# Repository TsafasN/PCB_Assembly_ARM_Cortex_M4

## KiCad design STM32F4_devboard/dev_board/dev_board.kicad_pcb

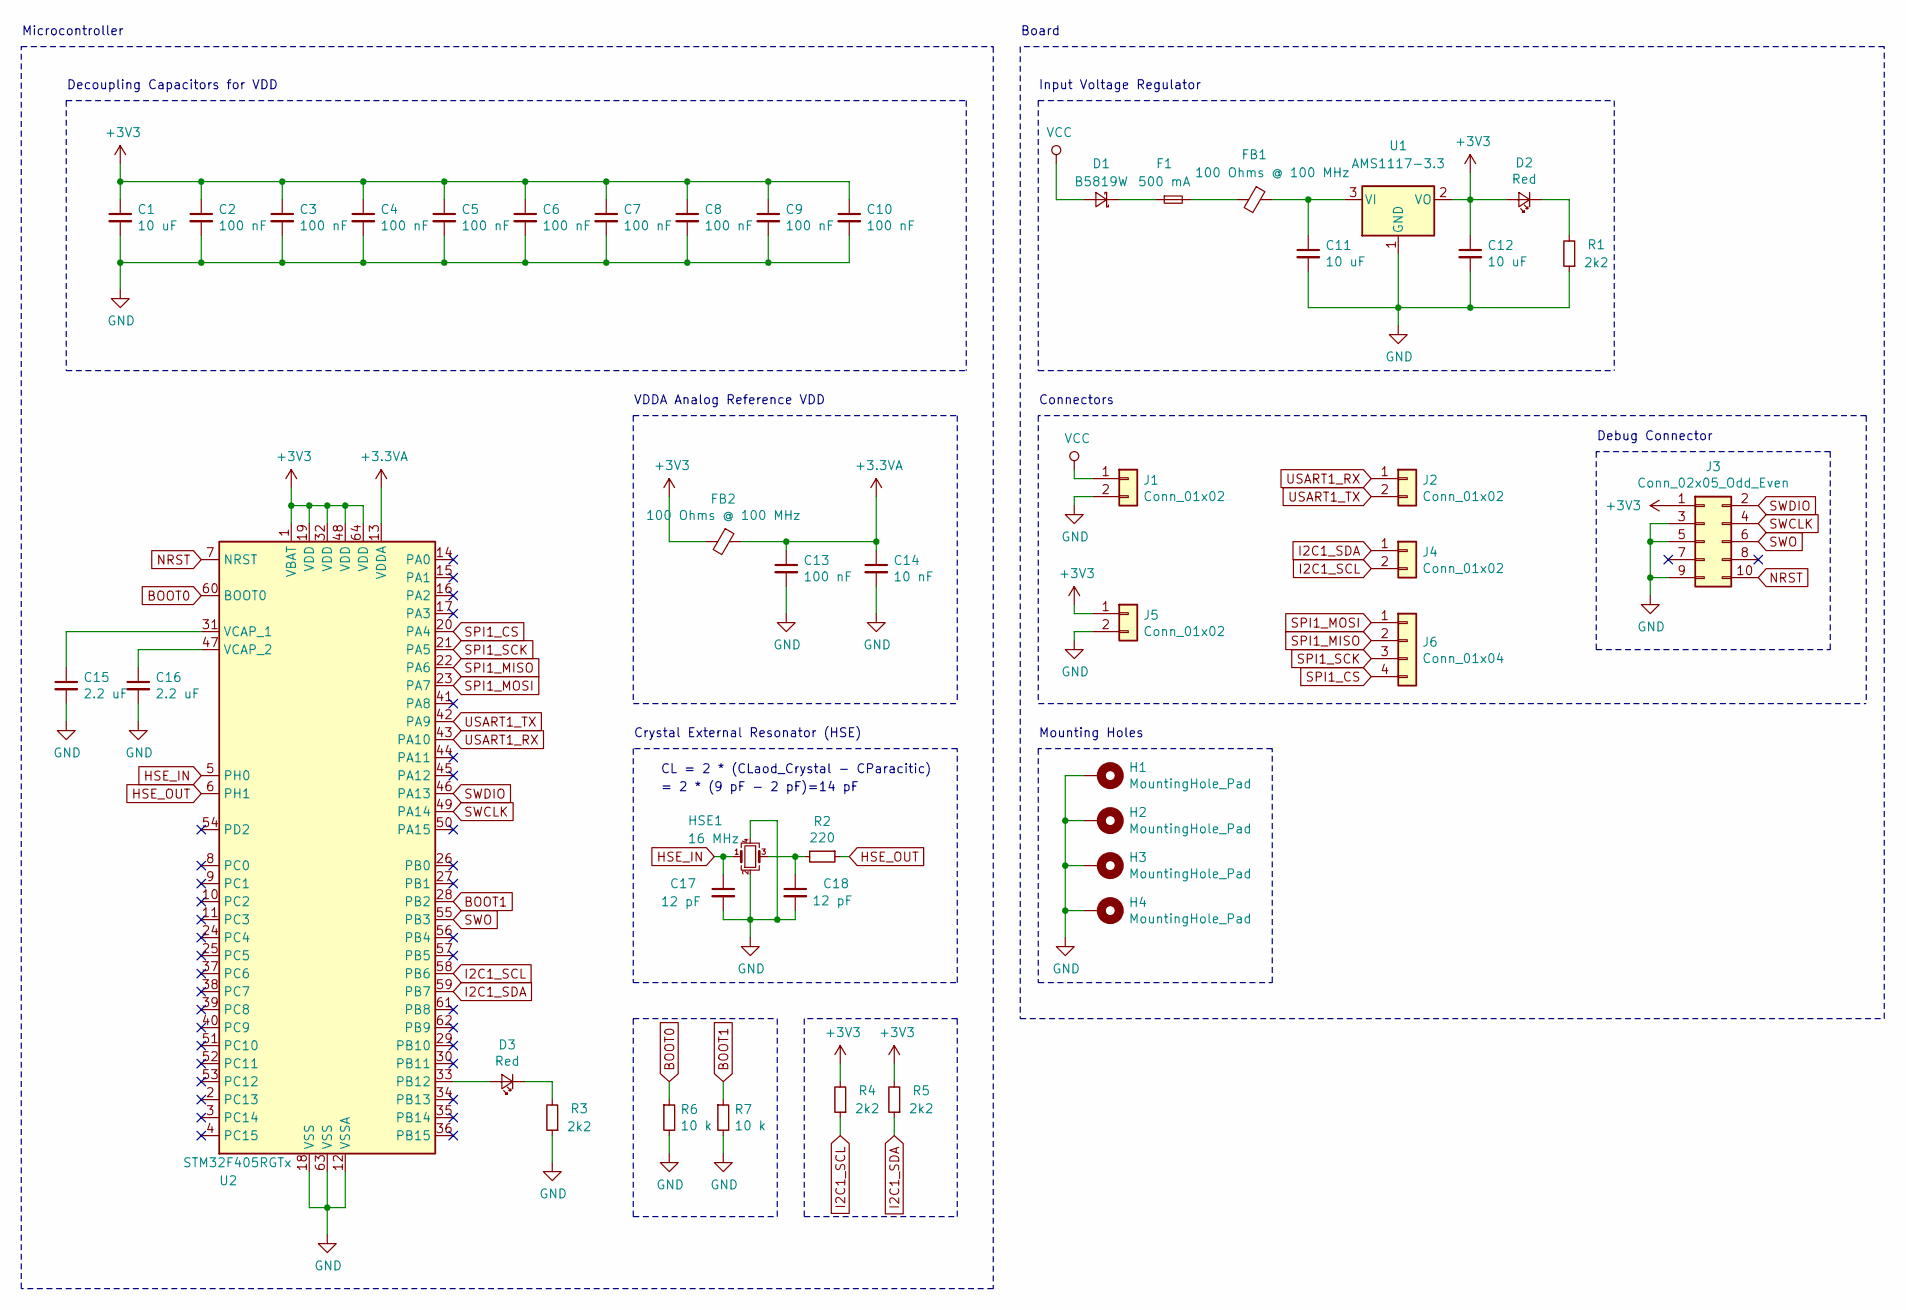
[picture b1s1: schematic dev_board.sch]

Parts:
C1: 10 uF; C_0603_1608Metric
C2, C3, C4, C5, C6, C7, C8, C9, C10, C13: 100 nF; C_0402_1005Metric
C11, C12: 10 uF; C_0805_2012Metric
C14: 10 nF; C_0402_1005Metric
C15, C16: 2.2 uF; C_0603_1608Metric
C17, C18: 12 pF; C_0402_1005Metric
D1: B5819W; D_SOD-123
D2, D3: Red; LED_0603_1608Metric
F1: 500 mA; Fuse_0603_1608Metric
FB1, FB2: 100 Ohms @ 100 MHz; L_0805_2012Metric
H1, H2, H3, H4: MountingHole_Pad; MountingHole_4.3mm_M4_Pad_Via
HSE1: 16 MHz; Crystal_SMD_3225-4Pin_3.2x2.5mm
J1, J2, J4, J5: Conn_01x02; PinHeader_1x02_P2.54mm_Vertical
J3: Conn_02x05_Odd_Even; PinHeader_2x05_P1.27mm_Vertical_SMD
J6: Conn_01x04; PinHeader_1x04_P2.54mm_Vertical
R1, R3: 2k2; R_0603_1608Metric
R2: 220; R_0402_1005Metric
R4, R5: 2k2; R_0402_1005Metric
R6, R7: 10 k; R_0402_1005Metric
U1: AMS1117-3.3; SOT-223-3_TabPin2
U2: STM32F405RGTx; LQFP-64_10x10mm_P0.5mm

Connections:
+3.3VA: C13.1, C14.1, FB2.1, U2.13 (VDDA)
+3V3: C1.1, C2.1, C3.1, C4.1, C5.1, C6.1, C7.1, C8.1, C9.1, C10.1, C12.1, D2.2 (A), FB2.2, J3.1, J5.1, R4.2, R5.2, U1.2 (VO), U2.1 (VBAT), U2.19 (VDD), U2.32 (VDD), U2.48 (VDD), U2.64 (VDD)
BOOT0: R6.1, U2.60 (BOOT0)
BOOT1: R7.1, U2.28 (PB2)
GND: C1.2, C2.2, C3.2, C4.2, C5.2, C6.2, C7.2, C8.2, C9.2, C10.2, C11.2, C12.2, C13.2, C14.2, C15.2, C16.2, C17.2, C18.2, H1.1, H2.1, H3.1, H4.1, HSE1.2, HSE1.4, J1.2, J3.3, J3.5, J3.9, J5.2, R1.1, R3.1, R6.2, R7.2, U1.1 (GND), U2.12 (VSSA), U2.18 (VSS), U2.63 (VSS)
HSE_IN: C17.1, HSE1.1, U2.5 (PH0)
HSE_OUT: R2.1, U2.6 (PH1)
I2C1_SCL: J4.2, R4.1, U2.58 (PB6)
I2C1_SDA: J4.1, R5.1, U2.59 (PB7)
NRST: J3.10, U2.7 (NRST)
unnamed: C11.1, FB1.1, U1.3 (VI)
unnamed: C15.1, U2.31 (VCAP_1)
unnamed: C16.1, U2.47 (VCAP_2)
unnamed: C18.1, HSE1.3, R2.2
unnamed: D1.1 (K), F1.1
unnamed: D2.1 (K), R1.2
unnamed: D3.1 (K), R3.2
unnamed: D3.2 (A), U2.33 (PB12)
unnamed: F1.2, FB1.2
SPI1_CS: J6.4, U2.20 (PA4)
SPI1_MISO: J6.2, U2.22 (PA6)
SPI1_MOSI: J6.1, U2.23 (PA7)
SPI1_SCK: J6.3, U2.21 (PA5)
SWCLK: J3.4, U2.49 (PA14)
SWDIO: J3.2, U2.46 (PA13)
SWO: J3.6, U2.55 (PB3)
USART1_RX: J2.1, U2.43 (PA10)
USART1_TX: J2.2, U2.42 (PA9)
VCC: D1.2 (A), J1.1

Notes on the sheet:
Input Voltage Regulator
Decoupling Capacitors for VDD
VDDA Analog Reference VDD
CL = 2 * (CLaod_Crystal - CParacitic)
= 2 * (9 pF - 2 pF)=14 pF
Crystal External Resonator (HSE)
Debug Connector
Microcontroller
Connectors
Mounting Holes
Board

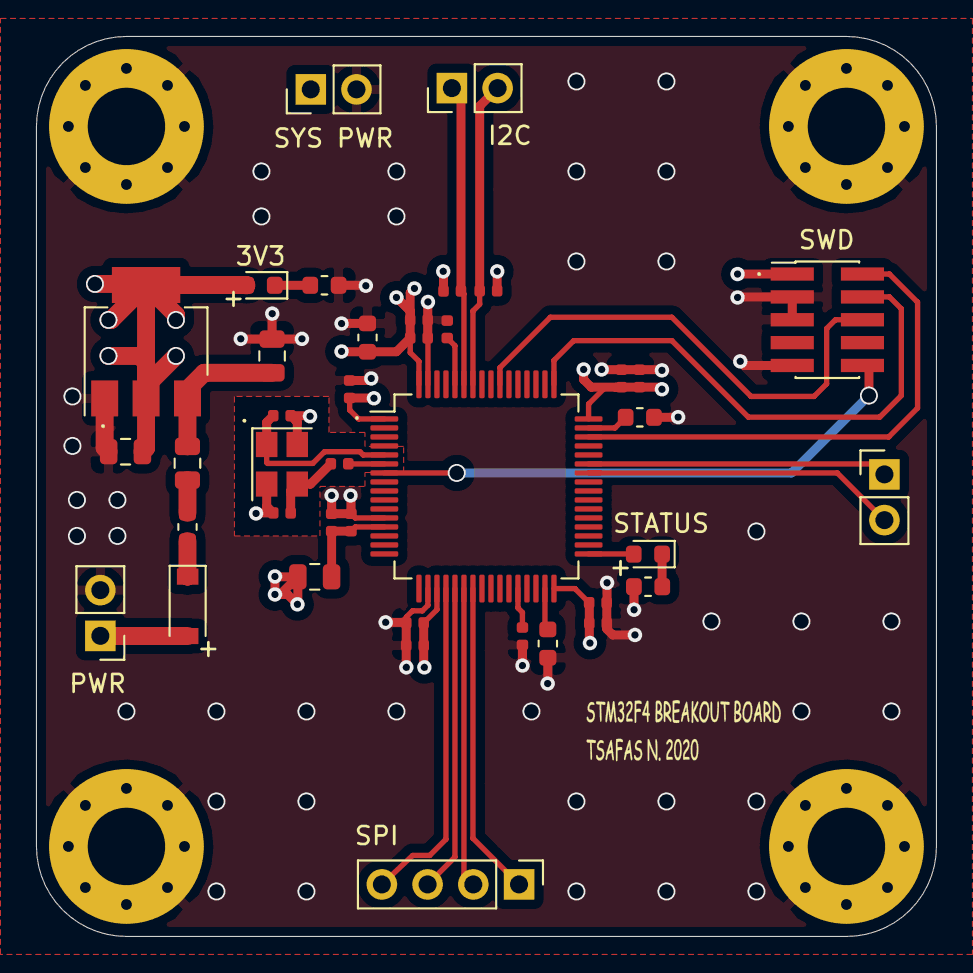
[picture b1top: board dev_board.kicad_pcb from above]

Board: 4 copper layers, 50.0 x 50.0 mm, 44 parts (0 on the bottom side), 29 nets.

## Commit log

2020-09-21 Added test.txt
2020-09-26 Added Hello to test.txt
